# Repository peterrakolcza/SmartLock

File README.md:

# 🔒 Smart Lock with Home Key support🔒

A smart lock built using ESP8266, an affordable microcontroller with WiFi capabilities, that can be controlled through a mobile app or web interface.

### Features

- 📱 Remote control of lock through app or web interface
- 🔐 Native Apple Home support with the HomeKey-ESP32 reader, or Homebridge
- 🕰️ Real-time status updates
- 💳 Optional Home Key support with an ESP32 + PN532 reader. You don't need a Raspberry Pi
- 🔨 Easy installation, compatible with most standard locks
- 🌀 The key and thumb-turn turn freely with a single servo: a spiral coupling, no clutch, no fighting against the servo

<br>

## 💭 Inspiration

The whole idea came from a [hackaday.io](https://hackaday.io/project/11917-smart-lock) project, huge thanks for providing the basic STL files and logic. I tried to further improve the project and make it possible to integrate it into existing smart home ecosystems like Apple HomeKit.

### **Furthermore, the objectives were almost identical:**

- Device must be cheap. This means no expensive motors or sensors can be used.
- Device must be presentable. I don't want to see any cables, electronics not even the motor itself on my apartment door (since it is a very small apartment).
- No modifications on door itself. I am a tenant at this apartment right now so I can't modify anything that can't be fixed.
- It should be secure. Most of the RF devices are vulnerable to replay attacks, the lock should be safe enough.

|                Inspiration - hackaday.io                |                    Latest version               |
| :-----------------------------------------------------: | :---------------------------------------------: |
|  |   |

<br>

## 🚀 Getting Started

1. Clone the repository to your local machine.

```bash
git clone https://github.com/peterrakolcza/SmartLock.git
```

2. 3D print the [single-servo lock](3D%20printed%20case/spiral/README.md), or the original case
3. Order the custom PCB and the components from JLCPCB for example
4. Wait :(
5. Configure the parameters in [`code/smart_lock/smart_lock.ino`](code/smart_lock/smart_lock.ino)
```
#ifndef STASSID
#define STASSID "*****" // CHANGE THIS
#define STAPSK  "*****" // CHANGE THIS
#endif

#define HOMEKEY_MODE 1 // 0 = standalone, 1 = HomeKey reader connects directly, 2 = external MQTT broker
```
6. Flash the firmware with the Arduino IDE (libraries: *ArduinoJson*, *PubSubClient*) or PlatformIO (`cd code/smart_lock && pio run -t upload`)
7. Assemble the whole lock
8. No calibration needed:
     - Put the magnet in the thumb-turn adapter so it is in front of the reed sensor when the thumb-turn is in its home position (where the key can be inserted and removed).
     - Start with the door unlocked. Then lock it once and unlock it once (button, app or HTTP API). On these first two moves the lock keeps turning until the thumb-turn stops at its end stop, counts the turns with the reed sensor and remembers them.
     - From then on every move stops when the magnet has come round the learned number of times, so the thumb-turn always ends in the home position. Servo speed and supply voltage no longer matter.
     - If the magnet doesn't come round in time (door handle not lifted, bolt blocked), the lock stops, reports **jammed** (Apple Home shows a jam alert, the API returns `"state":"jammed"`) and never claims to be locked.
     - To learn again (another door, moved magnet): hold the side button while powering on. The LED flashes 3 times.
9. Use it standalone (button + HTTP API), add it to Apple Home with Home Key using the [HomeKey-ESP32 reader](homekey/README.md), or integrate it with Homebridge

<br>

## ⚡ Custom PCB

You can just order my custom PCB assembled and flash the firmware. After that, connecting the sensors and servo using the header pins are easy.

<br>

|                easyEDA                |                     PCB               |
| :-----------------------------------------------------: | :---------------------------------------------: |
|                |      |

<br>

## 🔌 Pinout

<br>

| Pin on ESP | Pin in code |  Funcionality  |
| :--------: | :---------: | :------------: |
|     D6     |      12     |  Servo signal  |
|     D7     |      13     |  Reed sensor   |
|     D2     |      4      |     Button     |
|     D1     |      5      |      LED       |
|     RX     |      3      | Hub hall sensor (A3144) |

<br>
<br>
<br>
<br>
<br>
<br>
<br>
<br>

## ⚠️ **Limitations**

A lift-up handle on a smart lock can introduce several challenges that affect usability, compatibility, and security. One primary issue is user convenience. The necessity to lift the handle adds an extra step to the process of locking or unlocking the door, which can be particularly inconvenient when users' hands are full, they are in a hurry, or when it's dark. This could prevent the smart lock to properly lock the door.

The lock now detects this: if the thumb-turn stops before the learned number of turns, it reports **jammed** instead of locked (Apple Home shows a jam alert). The lock never claims to be locked when it isn't, and the next lock command simply tries again.

<br>

<br>

## 🧭 v5: self-adhesive, universal, battery or USB powered

Designed end to end on this branch ([`docs/v5.md`](docs/v5.md), part list with AliExpress links in [`docs/v5-parts.md`](docs/v5-parts.md)): self-adhesive (3M VHB, nothing screwed to the door), universal (three base presets, an adapter with two screw jaws for most thumb-turns), in two versions, battery (1200 mAh pouch, USB-C charging) or USB powered, an N20 gearmotor with a self-locking worm over the spiral coupling, and Matter over Thread on an ESP32-C6. 78 × 63 mm from the door. The CAD passes 51 fit / motion / strength / printability checks, the PCB is generated, routed and DRC-checked in KiCad, and the firmware (ESP-IDF + esp-matter, Thread sleepy end device) builds; none of it is built and tested on a door yet.

<br>

## 🌀 Single servo, key turns freely

Without help, turning the key or the thumb-turn by hand means back-driving the servo gearbox. Here a **spiral coupling** sits between the servo and the thumb-turn: a pin runs in a 2.75-turn spiral groove under the servo hub. Inside the spiral the key turns freely, and only at its ends does the servo drive the lock. After every movement the servo backs off into the spiral, counted by a small hall sensor on the RX pin. It uses **one servo, has nothing to calibrate, and the V3 PCB is unchanged**. The case is 82 × 85 mm.

See [the single-servo lock guide](3D%20printed%20case/spiral/README.md) for how it works, the other options I considered, parts, wiring, assembly, and the CAD and firmware checks. The two-servo clutch version is on branch `feature/clutch`. The original case (`bottom`, `middle`, `cover_led`) is still in `3D printed case`.

<br>

## 📙 API

Example request to lock the door:

```bash
curl -X POST http://smartlock.local -H 'Content-Type: application/json' -d '{"state":"locked"}'
```

Example request to get the current state:

```bash
curl -X GET http://smartlock.local
```

Example response:

```json
{
  "state": "locked",
  "homekey": true
}
```

`homekey` is `true` while the HomeKey reader (or the external MQTT broker) is connected.

<br>

## 🏠 Homebridge integration

<br>

Homebridge allows you to integrate with smart home devices that do not natively support HomeKit. There are over 2,000 Homebridge plugins supporting thousands of different smart accessories.

Homebridge is a lightweight Node.js server you can run on your home network that emulates the iOS HomeKit API. It supports Plugins, which are community-contributed modules that provide a basic bridge from HomeKit to various 3rd-party APIs provided by manufacturers of "smart home" devices.

You have 2 options to integrate the smart lock to your existing Apple HomeKit smart home:

### Home Key (native Apple Home)

The lock works with [HomeKey-ESP32](https://github.com/rednblkx/HomeKey-ESP32) by [rednblkx](https://github.com/rednblkx). An ESP32 board with a PN532 NFC module shows up in Apple Home as a native lock with Home Key and Express mode, and it drives this lock over Wi-Fi. The lock firmware has a tiny built-in MQTT broker, so the reader connects straight to it and you don't need a Raspberry Pi, Homebridge or any server.

See the **[Home Key setup guide](homekey/README.md)** for parts, wiring, the 3D printed reader enclosure, and configuration.

Thanks to [kormax](https://github.com/kormax) for [apple-home-key-reader](https://github.com/kormax/apple-home-key-reader), which the previous Raspberry Pi version was based on and which made Home Key on DIY hardware possible.

<br>

### EspLock

The lock uses the [EspLock](https://github.com/volca/homebridge-esplock) Homebridge plugin to integrate it into the Apple HomeKit ecosystem. Huge thanks to [volca](https://github.com/volca)!

Example configuration, it is possible to use a static IP address or the hostname:

```json
{
  "accessories": [
    {
      "accessory": "EspLock",
      "name": "Front Door",
      "url": "http://smartlock.local"
    }
  ]
}
```

To disable autolock feature, delete the following function from the index.js file:

```js
setTimeout(function () {
  if (currentState == Characteristic.LockTargetState.UNSECURED) {
    self.lockservice.setCharacteristic(
      Characteristic.LockTargetState,
      Characteristic.LockTargetState.SECURED
    );
  }
}, 5000);
```

<br>

## Contributions

🙏 I welcome contributions from the community! If you have any ideas or suggestions, please open an issue or submit a pull request.

<br>

## License

This project is licensed under the MIT License. See LICENSE for more information.

<br>

## 💻 Contact

For any questions or concerns, please open an issue or contact me.

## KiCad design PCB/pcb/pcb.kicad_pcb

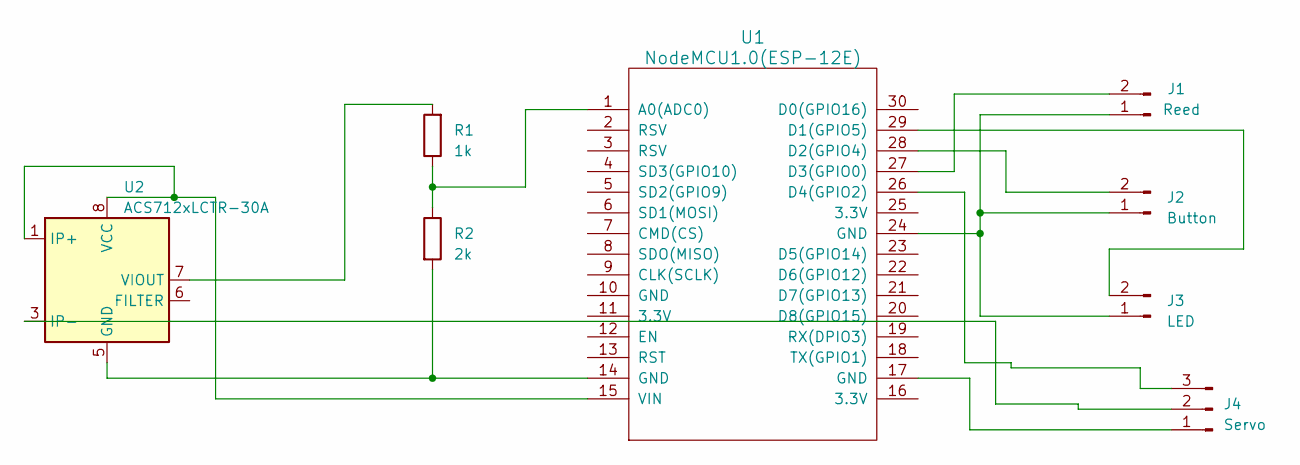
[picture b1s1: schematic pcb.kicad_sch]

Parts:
J1: Reed; PinHeader_1x02_P2.54mm_Vertical
J2: Button; PinHeader_1x02_P2.54mm_Vertical
J3: LED; PinHeader_1x02_P2.54mm_Vertical
J4: Servo; PinHeader_1x03_P2.54mm_Vertical
R1: 1k; R_Axial_DIN0411_L9.9mm_D3.6mm_P12.70mm_Horizontal
R2: 2k; R_Axial_DIN0411_L9.9mm_D3.6mm_P12.70mm_Horizontal
U1: NodeMCU1.0(ESP-12E); NodeMCU-LoLinV3
U2: ACS712xLCTR-30A; SOIC-8_3.9x4.9mm_P1.27mm

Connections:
unnamed: J1.1, J2.1, J3.1, U1.24 (GND)
unnamed: J1.2, U1.27 (D3(GPIO0))
unnamed: J2.2, U1.28 (D2(GPIO4))
unnamed: J3.2, U1.29 (D1(GPIO5))
unnamed: J4.1, U1.17 (GND)
unnamed: J4.2, U2.3 (IP-), U2.4 (IP-)
unnamed: J4.3, U1.26 (D4(GPIO2))
unnamed: R1.1, R2.1, U1.1 (A0(ADC0))
unnamed: U1.15 (VIN), U2.1 (IP+), U2.2 (IP+), U2.8 (VCC)
unnamed: R2.2, U1.14 (GND), U2.5 (GND)
unnamed: R1.2, U2.7 (VIOUT)

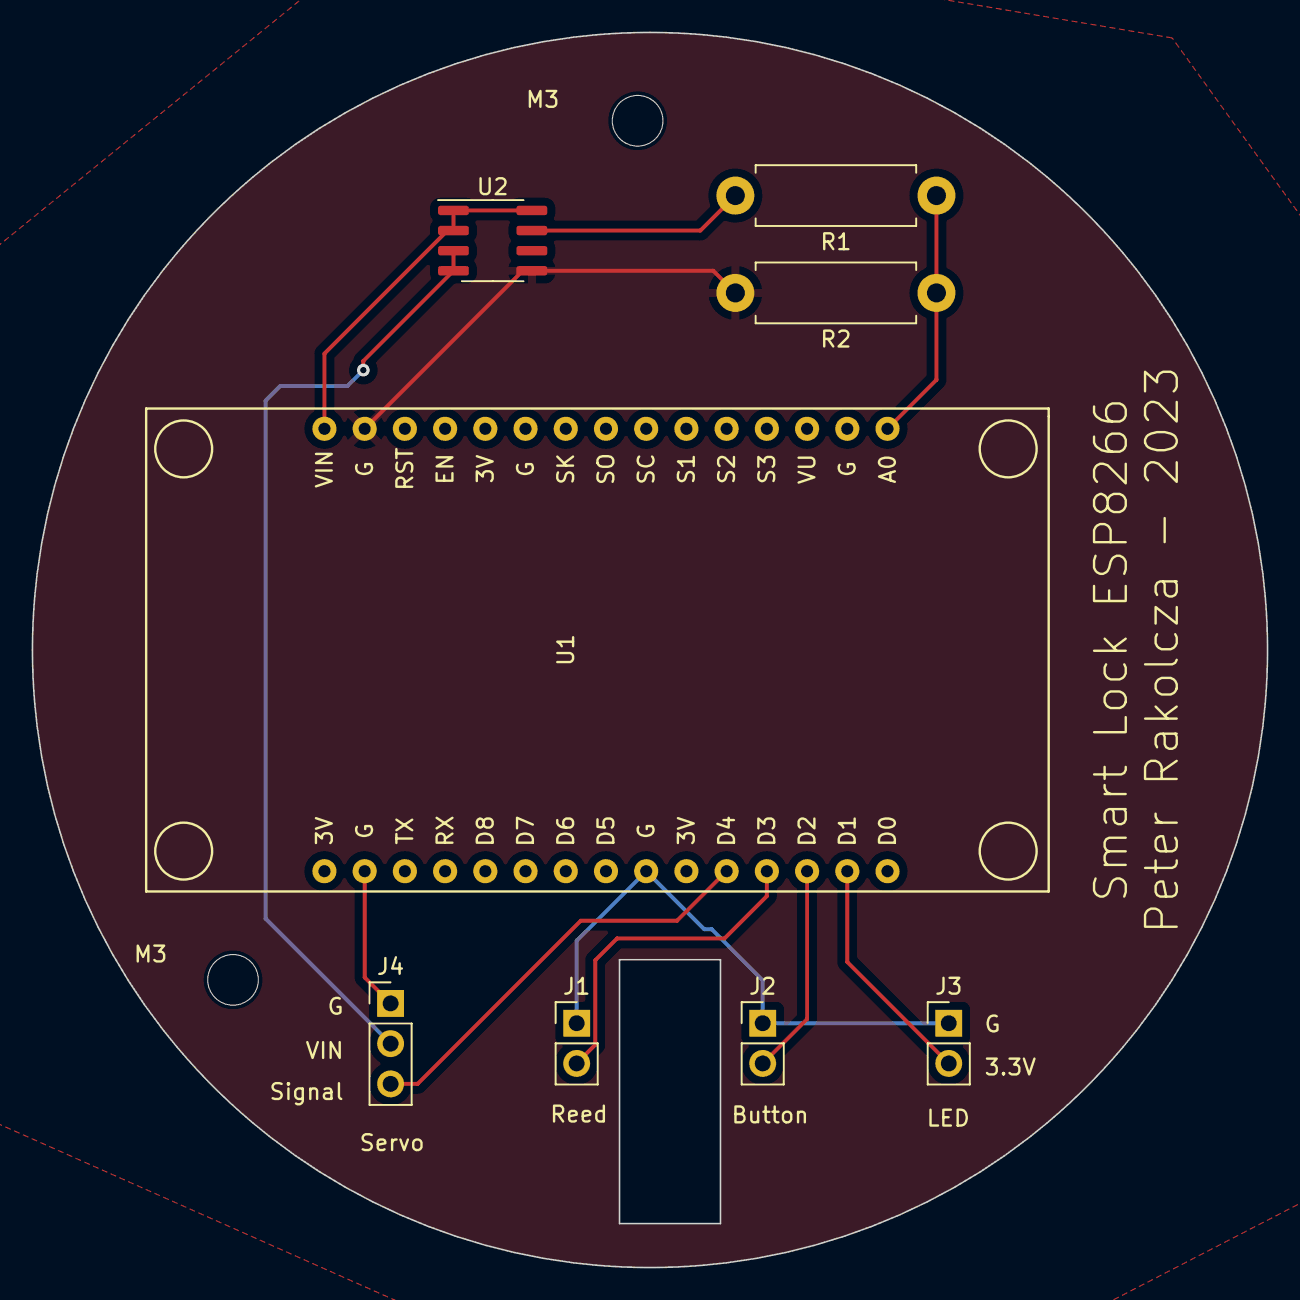
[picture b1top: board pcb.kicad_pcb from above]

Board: 2 copper layers, 78.0 x 78.0 mm, 10 parts (0 on the bottom side), 11 nets.

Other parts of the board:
M3, M3#2: MountingHole_3.2mm_M3

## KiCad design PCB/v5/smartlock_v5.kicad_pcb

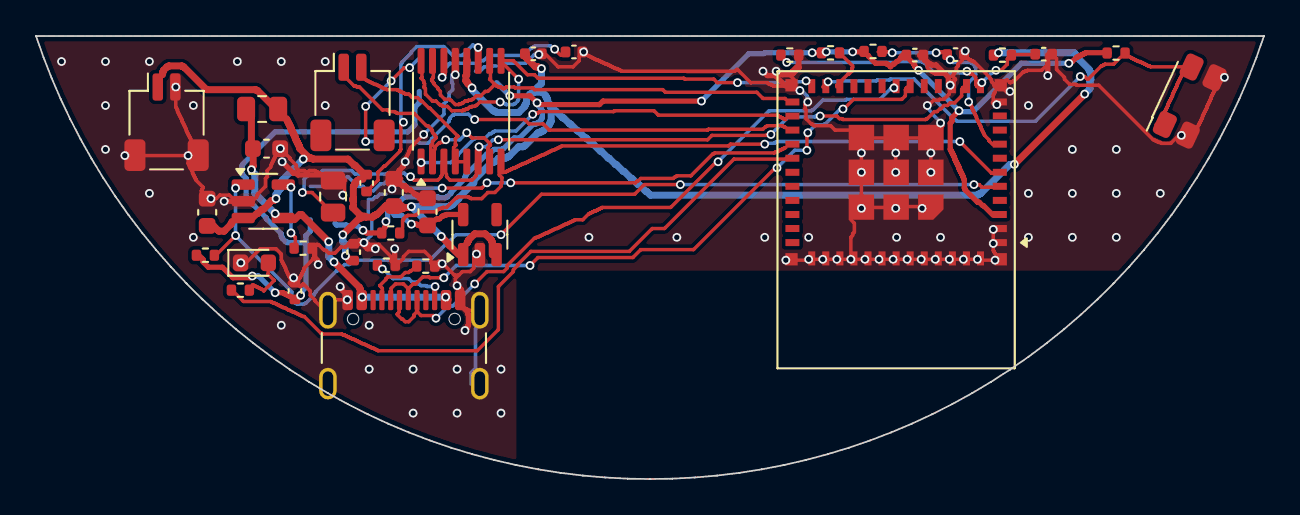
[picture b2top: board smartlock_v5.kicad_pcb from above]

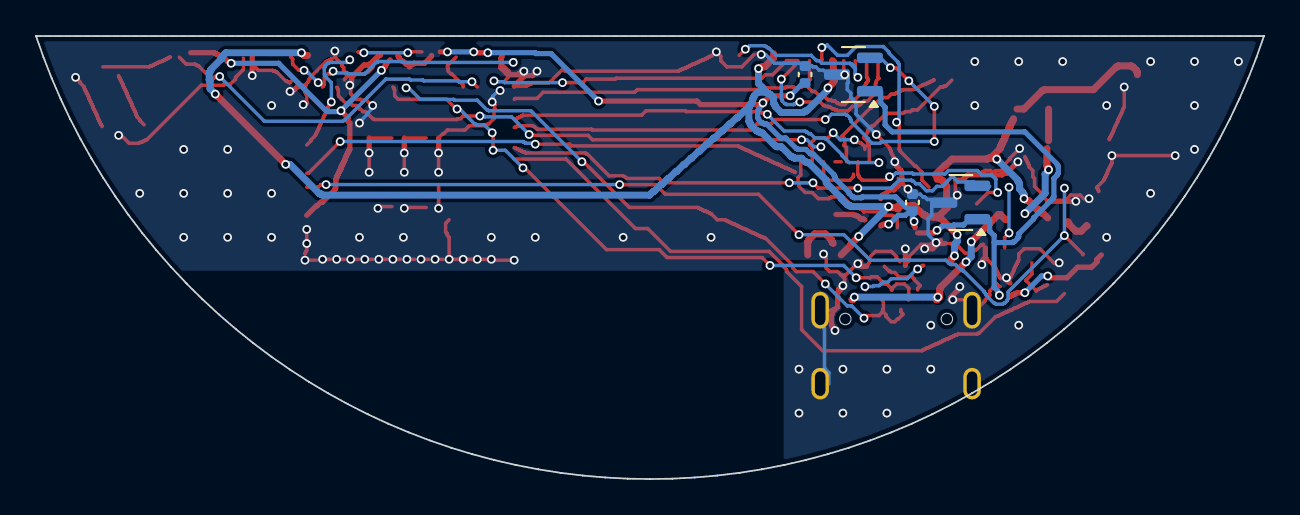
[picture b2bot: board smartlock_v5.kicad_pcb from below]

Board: 2 copper layers, 69.8 x 25.2 mm, 38 parts (4 on the bottom side), 27 nets.

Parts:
C1, C4: 10uF; C_0603_1608Metric
C2, C5, C12, C13, C14: 100nF; C_0402_1005Metric
C3, C10, C11: 1uF; C_0402_1005Metric
C6: 10nF; C_0402_1005Metric
C7: 2.2uF; C_0402_1005Metric
C8, C9: 4.7uF; C_0603_1608Metric
D1: status; LED_0603_1608Metric
J1: USB-C; USB_C_Receptacle_GCT_USB4105-xx-A_16P_TopMnt_Horizontal
J2: battery; JST_SH_SM02B-SRSS-TB_1x02-1MP_P1.00mm_Horizontal
J3: motor; JST_SH_SM02B-SRSS-TB_1x02-1MP_P1.00mm_Horizontal
R1, R2, R3, R6, R8: 10k; R_0402_1005Metric
R4: 1k; R_0402_1005Metric
R5: 0.15R; R_0805_2012Metric
R7: 2k; R_0402_1005Metric
R9, R10: 5.1k; R_0402_1005Metric
R11, R12: 1M; R_0402_1005Metric
R13: 0R; R_0805_2012Metric
SW1: button; SW_SPST_EVQP7A
U1: ESP32-C6-MINI-1-N4; ESP32-C6-MINI-1
U2: DRV8833PW; TSSOP-16_4.4x5mm_P0.65mm
U3: MCP73831-2; SOT-23-5
U4: RT9080-33; SOT-23-5
U5: DRV5032 (hub); SOT-23
U6: DRV5032 (thumb-turn); SOT-23

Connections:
3V3: C1.1, C2.1, C11.1, C13.1, C14.1, R1.1, R2.1, R3.1, R6.1, R8.1, U1.3, U4.5, U5.1, U6.1
BUTTON: R3.2, SW1.1, U1.23
CC1: J1.A5, R9.1
CC2: J1.B5, R10.1
CHG_STAT: R8.2, U1.5, U3.1
EN: C3.1, R1.2, U1.8
GND: C1.2, C2.2, C3.2, C4.2, C5.2, C7.2, C8.2, C9.2, C10.2, C11.2, C12.2, C13.2, C14.2, D1.1, J1.A1, J1.A12, J1.B1, J1.B12, J1.S1, J2.2, J2.MP, R5.2, R7.2, R9.2, R10.2, R12.2, SW1.2, U1.1, U1.2, U1.11, U1.14, U1.36, U1.37, U1.38, U1.39, U1.40, U1.41, U1.42, U1.43, U1.44, U1.45, U1.46, U1.47, U1.48, U1.49, U1.50, U1.51, U1.52, U1.53, U2.13, U3.2, U4.2, U5.3, U6.3
HALL_HUB: U1.27, U5.2
HALL_KNOB: U1.28, U6.2
ISENSE: R5.1, U1.13, U2.3, U2.6
LED: R4.1, U1.29
LED_A: D1.2, R4.2
MOTOR_FAULT: R6.2, U1.6, U2.8
MOTOR_IN1: U1.24, U2.9, U2.16
MOTOR_IN2: U1.25, U2.10, U2.15
MOTOR_SLEEP: U1.26, U2.1
MOT_A: J3.1, U2.2, U2.7
MOT_B: J3.2, U2.4, U2.5
PROG: R7.1, U3.5
STRAP_IO8: R2.2, U1.22
USB_DM: J1.A7, J1.B7, U1.17
USB_DP: J1.A6, J1.B6, U1.18
VBAT: C4.1, C5.1, C6.2, C9.1, C10.1, J2.1, R11.1, R13.2, U2.12, U3.3, U4.1, U4.3
VBAT_SENSE: C12.1, R11.2, R12.1, U1.12
VBUS: C8.1, J1.A4, J1.A9, J1.B4, J1.B9, R13.1, U3.4
VCP: C6.1, U2.11
VINT: C7.1, U2.14

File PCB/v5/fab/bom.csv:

Designator,Value,Footprint,Manufacturer part
"C1,C4",10uF,C_0603_1608Metric,CL10A106MQ8NNNC
"C2,C5,C12,C13,C14",100nF,C_0402_1005Metric,CL05B104KO5NNNC
"C3,C10,C11",1uF,C_0402_1005Metric,CL05A105KA5NQNC
C6,10nF,C_0402_1005Metric,CL05B103KB5NNNC
C7,2.2uF,C_0402_1005Metric,CL05A225MQ5NSNC
"C8,C9",4.7uF,C_0603_1608Metric,CL10A475KO8NNNC
D1,status,LED_0603_1608Metric,LED 0603 white
J1,USB-C,USB_C_Receptacle_GCT_USB4105-xx-A_16P_TopMnt_Horizontal,GCT USB4105-GF-A
J2,battery,JST_SH_SM02B-SRSS-TB_1x02-1MP_P1.00mm_Horizontal,JST SM02B-SRSS-TB
J3,motor,JST_SH_SM02B-SRSS-TB_1x02-1MP_P1.00mm_Horizontal,JST SM02B-SRSS-TB
"R1,R2,R3,R6,R8",10k,R_0402_1005Metric,0402WGF1002TCE
"R11,R12",1M,R_0402_1005Metric,0402WGF1004TCE
R4,1k,R_0402_1005Metric,0402WGF1001TCE
R5,0.15R,R_0805_2012Metric,RL1220S-R15-F
R7,2k,R_0402_1005Metric,0402WGF2001TCE
"R9,R10",5.1k,R_0402_1005Metric,0402WGF5101TCE
SW1,button,SW_SPST_EVQP7A,Panasonic EVQ-P7A01P
U1,ESP32-C6-MINI-1-N4,ESP32-C6-MINI-1,ESP32-C6-MINI-1-N4
U2,DRV8833PW,TSSOP-16_4.4x5mm_P0.65mm,DRV8833PWR
U3,MCP73831-2,SOT-23-5,MCP73831T-2ACI/OT
U4,RT9080-33,SOT-23-5,RT9080-33GJ5
U5,DRV5032 (hub),SOT-23,DRV5032FBDBZR
U6,DRV5032 (thumb-turn),SOT-23,DRV5032FBDBZR

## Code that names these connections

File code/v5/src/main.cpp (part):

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using namespace chip::app::Clusters;

// Pins: PCB/v5/layout.py GPIO
static const int PIN_VBAT_SENSE = 0;
static const int PIN_ISENSE = 1;
static const int PIN_CHG_STAT = 2;
static const int PIN_MOTOR_FAULT = 3;
static const int PIN_BUTTON = 9;
static const int PIN_MOTOR_IN1 = 18;
static const int PIN_MOTOR_IN2 = 19;
static const int PIN_MOTOR_SLEEP = 20;
static const int PIN_HALL_HUB = 21;
static const int PIN_HALL_KNOB = 22;
static const int PIN_LED = 23;

static const uint32_t BATTERY_INTERVAL_MS = 10UL * 60 * 1000;
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// ------------------------------------------------------------------------------------------------- hardware
static void motorRun(int direction) {
  // DRV8833, both bridges in parallel: IN1 / IN2 high-low = forward, low-high = reverse, low-low = coast
  digitalWrite(PIN_MOTOR_IN1, direction > 0 ? HIGH : LOW);
  digitalWrite(PIN_MOTOR_IN2, direction < 0 ? HIGH : LOW);
}

static void motorPower(bool on) {
  digitalWrite(PIN_MOTOR_SLEEP, on ? HIGH : LOW);   // nSLEEP: the driver draws < 1 uA asleep
  if (on) delay(2);
}

static bool knobActive() { return digitalRead(PIN_HALL_KNOB) == LOW; }  // DRV5032 pulls low in a field
static bool hubActive() { return digitalRead(PIN_HALL_HUB) == LOW; }

static uint8_t batteryPercent() {
  uint32_t mv = analogReadMilliVolts(PIN_VBAT_SENSE) * 2;      // 1 M / 1 M divider
  int percent = map((long)mv, 3300, 4150, 0, 100);
  return (uint8_t)constrain(percent, 0, 100);
}
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// instead of polling every 20 ms.
#if CONFIG_PM_ENABLE
static SemaphoreHandle_t wakeSignal;
static const int WAKE_PINS[] = {PIN_BUTTON, PIN_HALL_KNOB};

static void IRAM_ATTR onWakePin(void *arg) {
  gpio_intr_disable((gpio_num_t)(intptr_t)arg);
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// ------------------------------------------------------------------------------------------------- main
void setup() {
  Serial.begin(115200);
  pinMode(PIN_MOTOR_IN1, OUTPUT);
  pinMode(PIN_MOTOR_IN2, OUTPUT);
  pinMode(PIN_MOTOR_SLEEP, OUTPUT);
  motorPower(false);
  motorRun(0);
  pinMode(PIN_HALL_HUB, INPUT);
  pinMode(PIN_HALL_KNOB, INPUT);
  pinMode(PIN_BUTTON, INPUT_PULLUP);
  pinMode(PIN_MOTOR_FAULT, INPUT_PULLUP);
  pinMode(PIN_CHG_STAT, INPUT_PULLUP);
  pinMode(PIN_LED, OUTPUT);
  analogSetPinAttenuation(PIN_VBAT_SENSE, ADC_11db);

  prefs.begin("lock");
  locked = prefs.getBool("locked", true);
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
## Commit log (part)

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2023-02-07 added V1 files
2023-02-07 cleaned up the folder
2023-02-07 added images
2023-02-08 updated the documentation
2023-02-10 small changes
2023-02-14 updated the readme
2023-02-14 updated the readme, added pictures
2023-02-14 added V1 images
2023-02-20 started PCB design
2023-02-21 updated the PCB
2023-02-22 finished PCB design
2023-02-25 updated PCB design
2023-06-05 testing V3
2024-05-22 adding files for V3 update
2024-05-26 updated documentation for the latest version
2024-05-26 added more source files
2024-08-24 small upgrades and bug fixes
